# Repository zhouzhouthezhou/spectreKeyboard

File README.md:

# spectreKeyboard

Based off [design](https://wiki.ai03.com/) by ai03  
Inspiration from [Mysterium TKL](https://github.com/coseyfannitutti/mysterium)

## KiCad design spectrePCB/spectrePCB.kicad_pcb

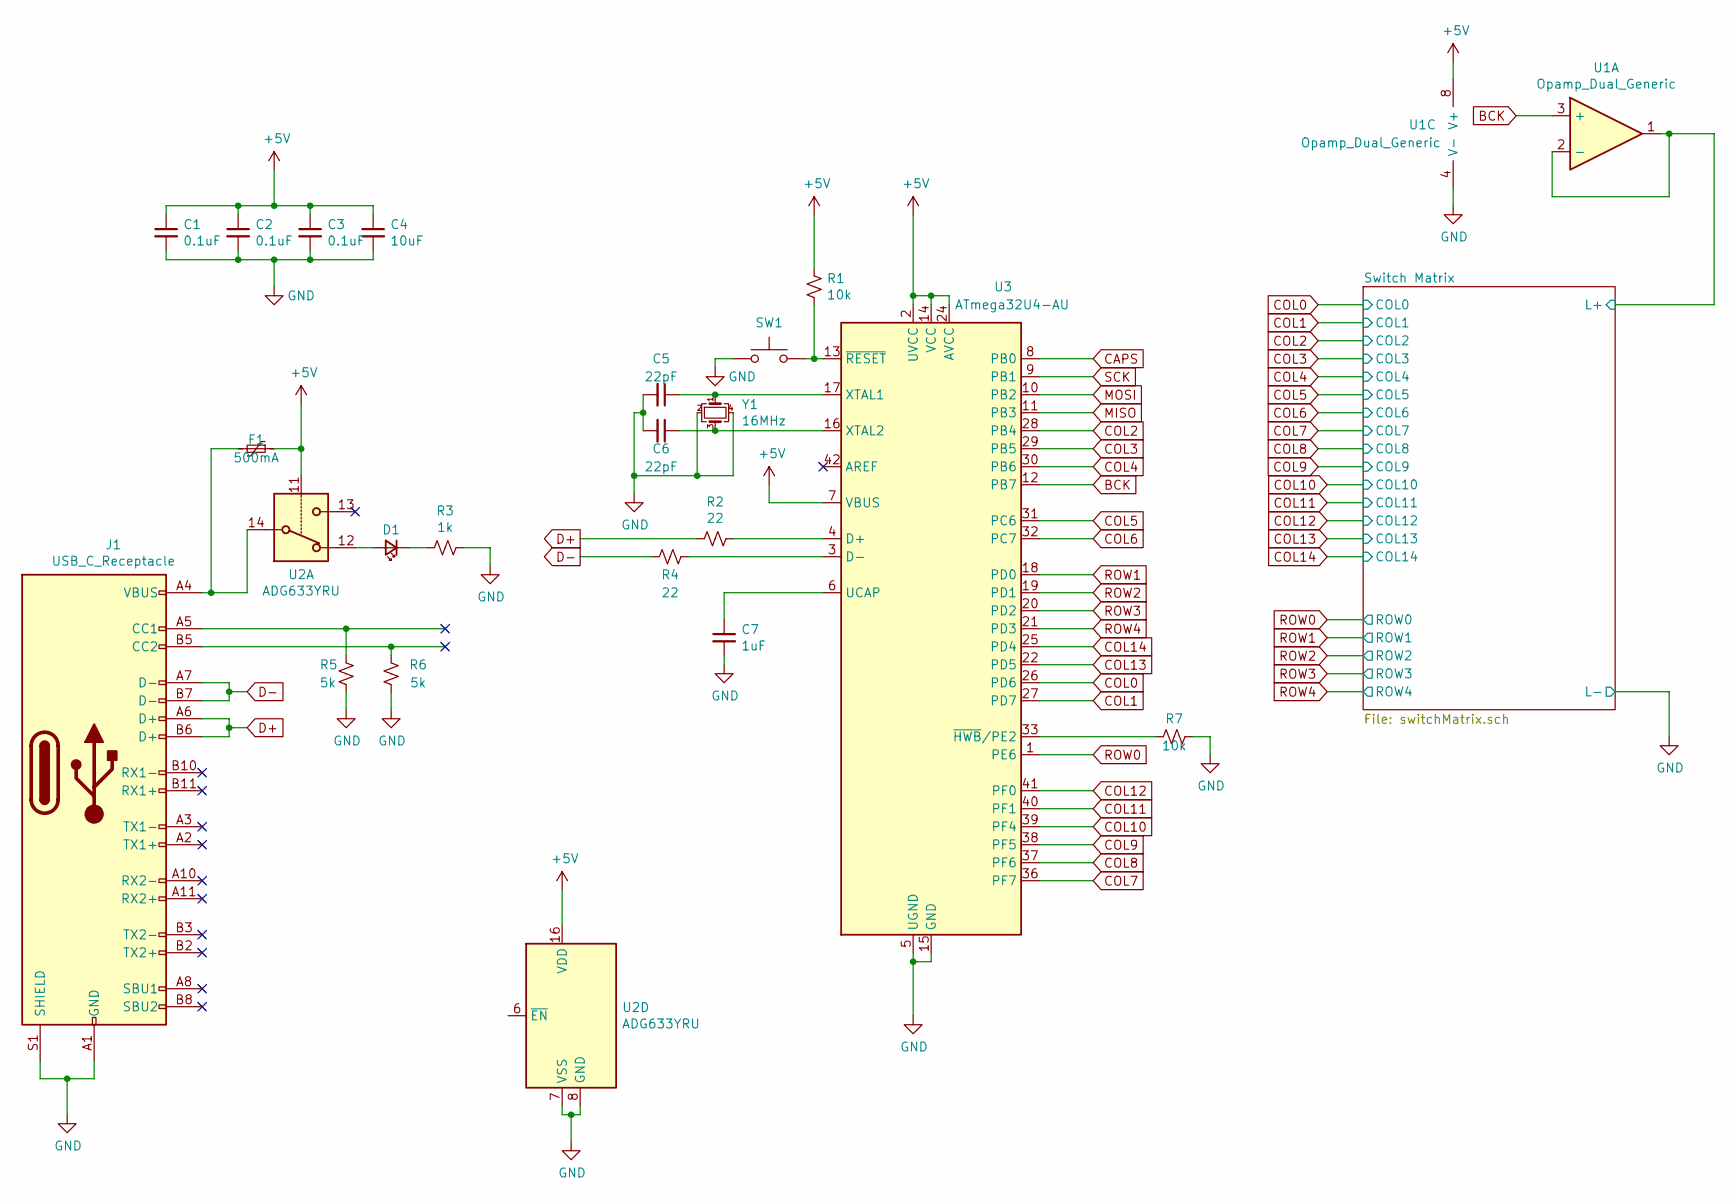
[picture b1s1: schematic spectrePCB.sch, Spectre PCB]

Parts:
C1, C2, C3: 0.1uF; C_0603_1608Metric
C4: 10uF; C_0603_1608Metric
C5, C6: 22pF; C_0603_1608Metric
C7: 1uF; C_0603_1608Metric
D1: LED_Red; LED_0603_1608Metric
F1: 500mA; Fuse_0603_1608Metric
J1: USB_C_Receptacle; USB_C_Receptacle_Amphenol_12401548E4-2A
R1, R7: 10k; R_0603_1608Metric
R2, R4: 22; R_0603_1608Metric
R3: 1k; R_0603_1608Metric
R5, R6: 5k; R_0603_1608Metric
SW1: SW_Push; SW_SPST_TL3305A
U1: Opamp_Dual_Generic; SOIC-8_3.9x4.9mm_P1.27mm
U2: ADG633YRU; TSSOP-20_4.4x6.5mm_P0.65mm
U3: ATmega32U4-AU; TQFP-44_10x10mm_P0.8mm
Y1: 16MHz; Crystal_SMD_3225-4Pin_3.2x2.5mm

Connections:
+5V: C1.1, C2.1, C3.1, C4.1, F1.1, R1.1, U1.8 (V+), U2.11, U2.16 (VDD), U3.2 (UVCC), U3.7 (VBUS), U3.14 (VCC), U3.24 (AVCC), U3.34 (VCC), U3.44 (AVCC); also elsewhere on the board
/Switch Matrix/L+: U1.1, U1.2 (-); also elsewhere on the board
BCK: U1.3 (+), U3.12 (PB7)
COL0: U3.26 (PD6); also elsewhere on the board
COL1: U3.27 (PD7); also elsewhere on the board
COL2: U3.28 (PB4); also elsewhere on the board
COL3: U3.29 (PB5); also elsewhere on the board
COL4: U3.30 (PB6); also elsewhere on the board
COL5: U3.31 (PC6); also elsewhere on the board
COL6: U3.32 (PC7); also elsewhere on the board
COL7: U3.36 (PF7); also elsewhere on the board
COL8: U3.37 (PF6); also elsewhere on the board
COL9: U3.38 (PF5); also elsewhere on the board
COL10: U3.39 (PF4); also elsewhere on the board
COL11: U3.40 (PF1); also elsewhere on the board
COL12: U3.41 (PF0); also elsewhere on the board
COL13: U3.22 (PD5); also elsewhere on the board
COL14: U3.25 (PD4); also elsewhere on the board
D+: J1.A6 (D+), J1.B6 (D+), R2.2
D-: J1.A7 (D-), J1.B7 (D-), R4.2
GND: C1.2, C2.2, C3.2, C4.2, C5.2, C6.2, C7.2, J1.A1 (GND), J1.A12 (GND), J1.B1 (GND), J1.B12 (GND), J1.S1 (SHIELD), R3.1, R5.1, R6.1, R7.1, SW1.1, U1.4 (V-), U2.7 (VSS), U2.8 (GND), U3.5 (UGND), U3.15 (GND), U3.23 (GND), U3.35 (GND), U3.43 (GND), Y1.2, Y1.4; also elsewhere on the board
unnamed: C5.1, U3.17 (XTAL1), Y1.1
unnamed: C6.1, U3.16 (XTAL2), Y1.3
unnamed: C7.1, U3.6 (UCAP)
unnamed: D1.1 (K), R3.2
unnamed: D1.2 (A), U2.12
unnamed: F1.2, J1.A4 (VBUS), J1.A9 (VBUS), J1.B4 (VBUS), J1.B9 (VBUS), U2.14
unnamed: J1.A5 (CC1), R5.2
unnamed: J1.B5 (CC2), R6.2
unnamed: R1.2, SW1.2, U3.13 (~RESET)
unnamed: R2.1, U3.4 (D+)
unnamed: R4.1, U3.3 (D-)
unnamed: R7.2, U3.33 (~HWB~/PE2)
ROW0: U3.1 (PE6); also elsewhere on the board
ROW1: U3.18 (PD0); also elsewhere on the board
ROW2: U3.19 (PD1); also elsewhere on the board
ROW3: U3.20 (PD2); also elsewhere on the board
ROW4: U3.21 (PD3); also elsewhere on the board

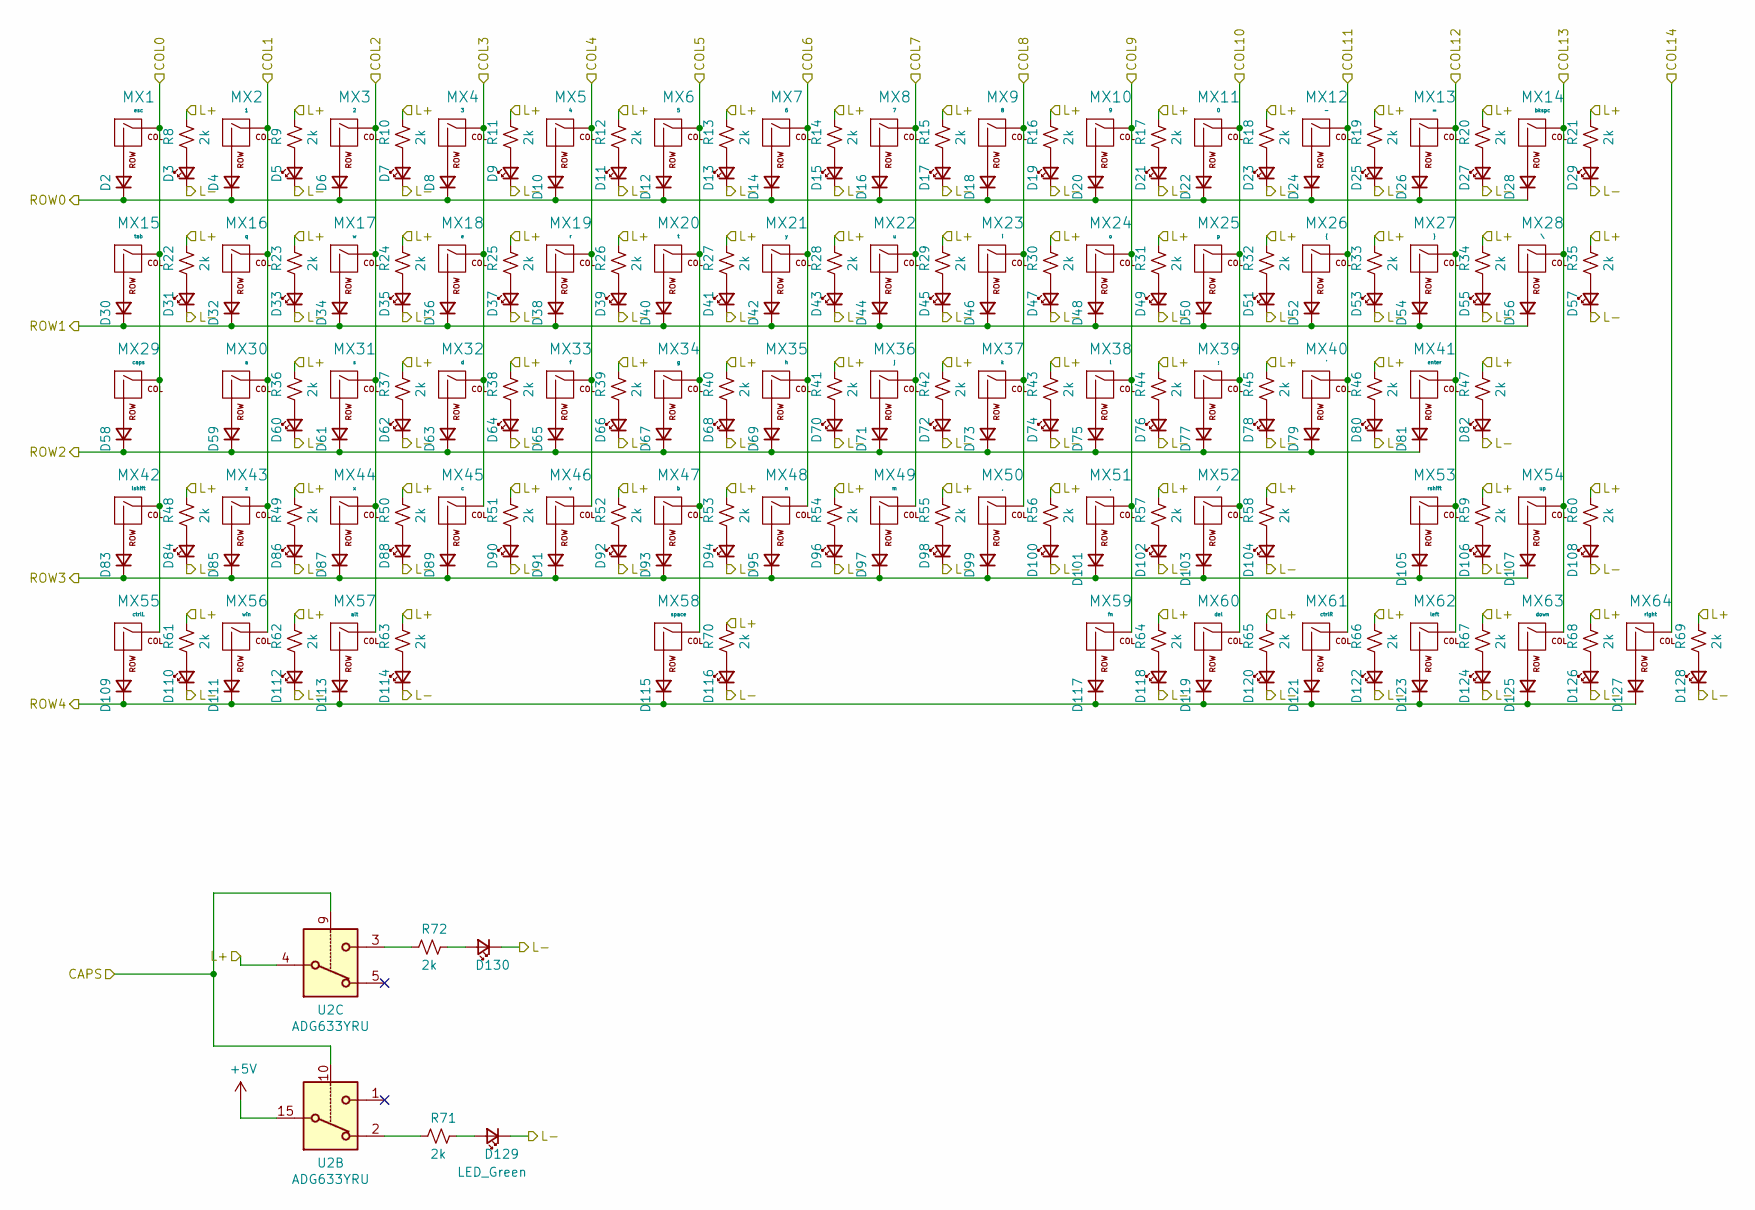
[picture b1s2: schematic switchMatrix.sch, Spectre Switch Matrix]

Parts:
D2, D4, D6, D8, D10, D12, D14, D16, D18, D20, D22, D24, D26, D28, D30, D32, D34, D36, D38, D40, D42, D44, D46, D48, D50, D52, D54, D56, D58, D59, D61, D63, D65, D67, D69, D71, D73, D75, D77, D79, D81, D83, D85, D87, D89, D91, D93, D95, D97, D99, D101, D103, D105, D107, D109, D111, D113, D115, D117, D119, D121, D123, D125, D127: D_Small; D_0603_1608Metric
D3, D5, D7, D9, D11, D13, D15, D17, D19, D21, D23, D25, D27, D29, D31, D33, D35, D37, D39, D41, D43, D45, D47, D49, D51, D53, D55, D57, D60, D62, D64, D66, D68, D70, D72, D74, D76, D78, D80, D82, D84, D86, D88, D90, D92, D94, D96, D98, D100, D102, D104, D106, D108, D110, D112, D114, D116, D118, D120, D122, D124, D126, D128, D130: LED_White; LED_0603_1608Metric
D129: LED_Green; LED_0603_1608Metric
MX1: esc; MX-1U-NoLED
MX2: 1; MX-1U-NoLED
MX3: 2; MX-1U-NoLED
MX4: 3; MX-1U-NoLED
MX5: 4; MX-1U-NoLED
MX6: 5; MX-1U-NoLED
MX7: 6; MX-1U-NoLED
MX8: 7; MX-1U-NoLED
MX9: 8; MX-1U-NoLED
MX10: 9; MX-1U-NoLED
MX11: 0; MX-1U-NoLED
MX12: -; MX-1U-NoLED
MX13: =; MX-1U-NoLED
MX14: bkspc; MX-2U-NoLED
MX15: tab; MX-1.5U-NoLED
MX16: q; MX-1U-NoLED
MX17: w; MX-1U-NoLED
MX18: e; MX-1U-NoLED
MX19: r; MX-1U-NoLED
MX20: t; MX-1U-NoLED
MX21: y; MX-1U-NoLED
MX22: u; MX-1U-NoLED
MX23: i; MX-1U-NoLED
MX24: o; MX-1U-NoLED
MX25: p; MX-1U-NoLED
MX26: {; MX-1U-NoLED
MX27: }; MX-1U-NoLED
MX28: \\; MX-1.5U-NoLED
MX29: caps; MX-1.75U-NoLED
MX30: a; MX-1U-NoLED
MX31: s; MX-1U-NoLED
MX32: d; MX-1U-NoLED
MX33: f; MX-1U-NoLED
MX34: g; MX-1U-NoLED
MX35: h; MX-1U-NoLED
MX36: j; MX-1U-NoLED
MX37: k; MX-1U-NoLED
MX38: l; MX-1U-NoLED
MX39: ;; MX-1U-NoLED
MX40: '; MX-1U-NoLED
MX41: enter; MX-2.25U-NoLED
MX42: lshift; MX-2.25U-NoLED
MX43: z; MX-1U-NoLED
MX44: x; MX-1U-NoLED
MX45: c; MX-1U-NoLED
MX46: v; MX-1U-NoLED
MX47: b; MX-1U-NoLED
MX48: n; MX-1U-NoLED
MX49: m; MX-1U-NoLED
MX50: ,; MX-1U-NoLED
MX51: .; MX-1U-NoLED
MX52: /; MX-1U-NoLED
MX53: rshift; MX-2.75U-NoLED
MX54: up; MX-1U-NoLED
MX55: ctrlL; MX-1.25U-NoLED
MX56: win; MX-1.25U-NoLED
MX57: alt; MX-1.25U-NoLED
MX58: space; MX-6.25U-NoLED
MX59: fn; MX-1.25U-NoLED
MX60: del; MX-1.25U-NoLED
MX61: ctrlR; MX-1.25U-NoLED
MX62: left; MX-1U-NoLED
MX63: down; MX-1U-NoLED
MX64: right; MX-1U-NoLED
R8, R9, R10, R11, R12, R13, R14, R15, R16, R17, R18, R19, R20, R21, R22, R23, R24, R25, R26, R27, R28, R29, R30, R31, R32, R33, R34, R35, R36, R37, R38, R39, R40, R41, R42, R43, R44, R45, R46, R47, R48, R49, R50, R51, R52, R53, R54, R55, R56, R57, R58, R59, R60, R61, R62, R63, R64, R65, R66, R67, R68, R69, R70, R71, R72: 2k; R_0603_1608Metric
U2: ADG633YRU; TSSOP-20_4.4x6.5mm_P0.65mm

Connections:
+5V: U2.15; also elsewhere on the board
/Switch Matrix/CAPS: U2.9, U2.10
/Switch Matrix/L+: R8.1, R9.1, R10.1, R11.1, R12.1, R13.1, R14.1, R15.1, R16.1, R17.1, R18.1, R19.1, R20.1, R21.1, R22.1, R23.1, R24.1, R25.1, R26.1, R27.1, R28.1, R29.1, R30.1, R31.1, R32.1, R33.1, R34.1, R35.1, R36.1, R37.1, R38.1, R39.1, R40.1, R41.1, R42.1, R43.1, R44.1, R45.1, R46.1, R47.1, R48.1, R49.1, R50.1, R51.1, R52.1, R53.1, R54.1, R55.1, R56.1, R57.1, R58.1, R59.1, R60.1, R61.1, R62.1, R63.1, R64.1, R65.1, R66.1, R67.1, R68.1, R69.1, R70.1, U2.4; also elsewhere on the board
COL0: MX1.1 (COL), MX15.1 (COL), MX29.1 (COL), MX42.1 (COL), MX55.1 (COL); also elsewhere on the board
COL1: MX2.1 (COL), MX16.1 (COL), MX30.1 (COL), MX43.1 (COL), MX56.1 (COL); also elsewhere on the board
COL2: MX3.1 (COL), MX17.1 (COL), MX31.1 (COL), MX44.1 (COL), MX57.1 (COL); also elsewhere on the board
COL3: MX4.1 (COL), MX18.1 (COL), MX32.1 (COL), MX45.1 (COL); also elsewhere on the board
COL4: MX5.1 (COL), MX19.1 (COL), MX33.1 (COL), MX46.1 (COL); also elsewhere on the board
COL5: MX6.1 (COL), MX20.1 (COL), MX34.1 (COL), MX47.1 (COL), MX58.1 (COL); also elsewhere on the board
COL6: MX7.1 (COL), MX21.1 (COL), MX35.1 (COL), MX48.1 (COL); also elsewhere on the board
COL7: MX8.1 (COL), MX22.1 (COL), MX36.1 (COL), MX49.1 (COL); also elsewhere on the board
COL8: MX9.1 (COL), MX23.1 (COL), MX37.1 (COL), MX50.1 (COL); also elsewhere on the board
COL9: MX10.1 (COL), MX24.1 (COL), MX38.1 (COL), MX51.1 (COL), MX59.1 (COL); also elsewhere on the board
COL10: MX11.1 (COL), MX25.1 (COL), MX39.1 (COL), MX52.1 (COL), MX60.1 (COL); also elsewhere on the board
COL11: MX12.1 (COL), MX26.1 (COL), MX40.1 (COL), MX61.1 (COL); also elsewhere on the board
COL12: MX13.1 (COL), MX27.1 (COL), MX41.1 (COL), MX53.1 (COL), MX62.1 (COL); also elsewhere on the board
COL13: MX14.1 (COL), MX28.1 (COL), MX54.1 (COL), MX63.1 (COL); also elsewhere on the board
COL14: MX64.1 (COL); also elsewhere on the board
GND: D3.1 (K), D5.1 (K), D7.1 (K), D9.1 (K), D11.1 (K), D13.1 (K), D15.1 (K), D17.1 (K), D19.1 (K), D21.1 (K), D23.1 (K), D25.1 (K), D27.1 (K), D29.1 (K), D31.1 (K), D33.1 (K), D35.1 (K), D37.1 (K), D39.1 (K), D41.1 (K), D43.1 (K), D45.1 (K), D47.1 (K), D49.1 (K), D51.1 (K), D53.1 (K), D55.1 (K), D57.1 (K), D60.1 (K), D62.1 (K), D64.1 (K), D66.1 (K), D68.1 (K), D70.1 (K), D72.1 (K), D74.1 (K), D76.1 (K), D78.1 (K), D80.1 (K), D82.1 (K), D84.1 (K), D86.1 (K), D88.1 (K), D90.1 (K), D92.1 (K), D94.1 (K), D96.1 (K), D98.1 (K), D100.1 (K), D102.1 (K), D104.1 (K), D106.1 (K), D108.1 (K), D110.1 (K), D112.1 (K), D114.1 (K), D116.1 (K), D118.1 (K), D120.1 (K), D122.1 (K), D124.1 (K), D126.1 (K), D128.1 (K), D129.1 (K), D130.1 (K); also elsewhere on the board
unnamed: D2.2 (A), MX1.2 (ROW)
unnamed: D3.2 (A), R8.2
unnamed: D4.2 (A), MX2.2 (ROW)
unnamed: D5.2 (A), R9.2
unnamed: D6.2 (A), MX3.2 (ROW)
unnamed: D7.2 (A), R10.2
unnamed: D8.2 (A), MX4.2 (ROW)
unnamed: D9.2 (A), R11.2
unnamed: D10.2 (A), MX5.2 (ROW)
unnamed: D11.2 (A), R12.2
unnamed: D12.2 (A), MX6.2 (ROW)
unnamed: D13.2 (A), R13.2
unnamed: D14.2 (A), MX7.2 (ROW)
unnamed: D15.2 (A), R14.2
unnamed: D16.2 (A), MX8.2 (ROW)
unnamed: D17.2 (A), R15.2
unnamed: D18.2 (A), MX9.2 (ROW)
unnamed: D19.2 (A), R16.2
unnamed: D20.2 (A), MX10.2 (ROW)
unnamed: D21.2 (A), R17.2
unnamed: D22.2 (A), MX11.2 (ROW)
unnamed: D23.2 (A), R18.2
unnamed: D24.2 (A), MX12.2 (ROW)
unnamed: D25.2 (A), R19.2
unnamed: D26.2 (A), MX13.2 (ROW)
unnamed: D27.2 (A), R20.2
unnamed: D28.2 (A), MX14.2 (ROW)
unnamed: D29.2 (A), R21.2
unnamed: D30.2 (A), MX15.2 (ROW)
unnamed: D31.2 (A), R22.2
unnamed: D32.2 (A), MX16.2 (ROW)
unnamed: D33.2 (A), R23.2
unnamed: D34.2 (A), MX17.2 (ROW)
unnamed: D35.2 (A), R24.2
unnamed: D36.2 (A), MX18.2 (ROW)
unnamed: D37.2 (A), R25.2
unnamed: D38.2 (A), MX19.2 (ROW)
unnamed: D39.2 (A), R26.2
unnamed: D40.2 (A), MX20.2 (ROW)
unnamed: D41.2 (A), R27.2
unnamed: D42.2 (A), MX21.2 (ROW)
unnamed: D43.2 (A), R28.2
unnamed: D44.2 (A), MX22.2 (ROW)
unnamed: D45.2 (A), R29.2
unnamed: D46.2 (A), MX23.2 (ROW)
unnamed: D47.2 (A), R30.2
unnamed: D48.2 (A), MX24.2 (ROW)
unnamed: D49.2 (A), R31.2
unnamed: D50.2 (A), MX25.2 (ROW)
unnamed: D51.2 (A), R32.2
unnamed: D52.2 (A), MX26.2 (ROW)
unnamed: D53.2 (A), R33.2
unnamed: D54.2 (A), MX27.2 (ROW)
unnamed: D55.2 (A), R34.2
unnamed: D56.2 (A), MX28.2 (ROW)
unnamed: D57.2 (A), R35.2
unnamed: D58.2 (A), MX29.2 (ROW)
unnamed: D59.2 (A), MX30.2 (ROW)
unnamed: D60.2 (A), R36.2
unnamed: D61.2 (A), MX31.2 (ROW)
unnamed: D62.2 (A), R37.2
unnamed: D63.2 (A), MX32.2 (ROW)
unnamed: D64.2 (A), R38.2
unnamed: D65.2 (A), MX33.2 (ROW)
unnamed: D66.2 (A), R39.2
unnamed: D67.2 (A), MX34.2 (ROW)
unnamed: D68.2 (A), R40.2
unnamed: D69.2 (A), MX35.2 (ROW)
unnamed: D70.2 (A), R41.2
unnamed: D71.2 (A), MX36.2 (ROW)
unnamed: D72.2 (A), R42.2
unnamed: D73.2 (A), MX37.2 (ROW)
unnamed: D74.2 (A), R43.2
unnamed: D75.2 (A), MX38.2 (ROW)
unnamed: D76.2 (A), R44.2
unnamed: D77.2 (A), MX39.2 (ROW)
unnamed: D78.2 (A), R45.2
unnamed: D79.2 (A), MX40.2 (ROW)
unnamed: D80.2 (A), R46.2
unnamed: D81.2 (A), MX41.2 (ROW)
unnamed: D82.2 (A), R47.2
unnamed: D83.2 (A), MX42.2 (ROW)
unnamed: D84.2 (A), R48.2
unnamed: D85.2 (A), MX43.2 (ROW)
unnamed: D86.2 (A), R49.2
unnamed: D87.2 (A), MX44.2 (ROW)
unnamed: D88.2 (A), R50.2
unnamed: D89.2 (A), MX45.2 (ROW)
unnamed: D90.2 (A), R51.2
unnamed: D91.2 (A), MX46.2 (ROW)
unnamed: D92.2 (A), R52.2
unnamed: D93.2 (A), MX47.2 (ROW)
unnamed: D94.2 (A), R53.2
unnamed: D95.2 (A), MX48.2 (ROW)
unnamed: D96.2 (A), R54.2
unnamed: D97.2 (A), MX49.2 (ROW)
unnamed: D98.2 (A), R55.2
unnamed: D99.2 (A), MX50.2 (ROW)
unnamed: D100.2 (A), R56.2
unnamed: D101.2 (A), MX51.2 (ROW)
unnamed: D102.2 (A), R57.2
unnamed: D103.2 (A), MX52.2 (ROW)
unnamed: D104.2 (A), R58.2
unnamed: D105.2 (A), MX53.2 (ROW)
unnamed: D106.2 (A), R59.2
unnamed: D107.2 (A), MX54.2 (ROW)
unnamed: D108.2 (A), R60.2
unnamed: D109.2 (A), MX55.2 (ROW)
unnamed: D110.2 (A), R61.2
unnamed: D111.2 (A), MX56.2 (ROW)
unnamed: D112.2 (A), R62.2
unnamed: D113.2 (A), MX57.2 (ROW)
unnamed: D114.2 (A), R63.2
unnamed: D115.2 (A), MX58.2 (ROW)
unnamed: D116.2 (A), R70.2
unnamed: D117.2 (A), MX59.2 (ROW)
unnamed: D118.2 (A), R64.2
unnamed: D119.2 (A), MX60.2 (ROW)
unnamed: D120.2 (A), R65.2
unnamed: D121.2 (A), MX61.2 (ROW)
unnamed: D122.2 (A), R66.2
unnamed: D123.2 (A), MX62.2 (ROW)
unnamed: D124.2 (A), R67.2
unnamed: D125.2 (A), MX63.2 (ROW)
unnamed: D126.2 (A), R68.2
unnamed: D127.2 (A), MX64.2 (ROW)
unnamed: D128.2 (A), R69.2
unnamed: D129.2 (A), R71.1
unnamed: D130.2 (A), R72.1
unnamed: R71.2, U2.2
unnamed: R72.2, U2.3
ROW0: D2.1 (K), D4.1 (K), D6.1 (K), D8.1 (K), D10.1 (K), D12.1 (K), D14.1 (K), D16.1 (K), D18.1 (K), D20.1 (K), D22.1 (K), D24.1 (K), D26.1 (K), D28.1 (K); also elsewhere on the board
ROW1: D30.1 (K), D32.1 (K), D34.1 (K), D36.1 (K), D38.1 (K), D40.1 (K), D42.1 (K), D44.1 (K), D46.1 (K), D48.1 (K), D50.1 (K), D52.1 (K), D54.1 (K), D56.1 (K); also elsewhere on the board
ROW2: D58.1 (K), D59.1 (K), D61.1 (K), D63.1 (K), D65.1 (K), D67.1 (K), D69.1 (K), D71.1 (K), D73.1 (K), D75.1 (K), D77.1 (K), D79.1 (K), D81.1 (K); also elsewhere on the board
ROW3: D83.1 (K), D85.1 (K), D87.1 (K), D89.1 (K), D91.1 (K), D93.1 (K), D95.1 (K), D97.1 (K), D99.1 (K), D101.1 (K), D103.1 (K), D105.1 (K), D107.1 (K); also elsewhere on the board
ROW4: D109.1 (K), D111.1 (K), D113.1 (K), D115.1 (K), D117.1 (K), D119.1 (K), D121.1 (K), D123.1 (K), D125.1 (K), D127.1 (K); also elsewhere on the board

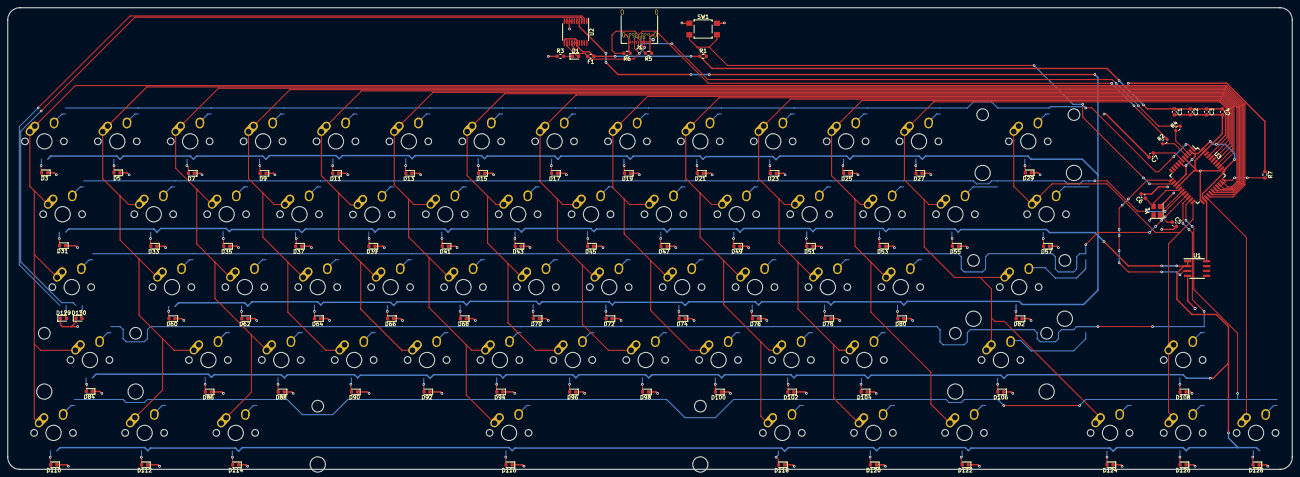
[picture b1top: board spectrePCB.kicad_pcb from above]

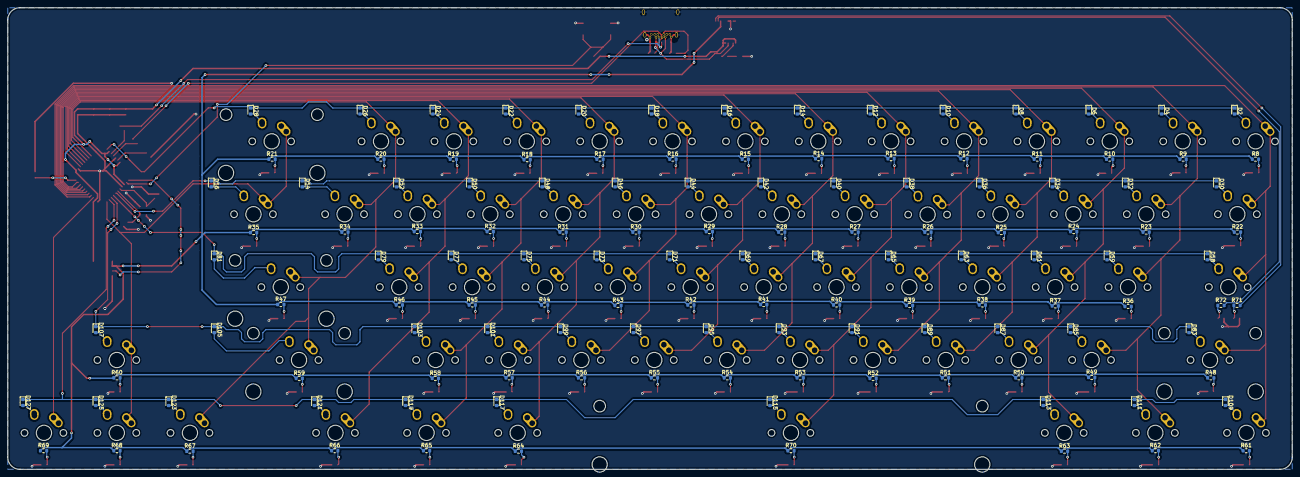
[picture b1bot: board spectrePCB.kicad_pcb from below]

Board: 2 copper layers, 335.8 x 120.7 mm, 280 parts (129 on the bottom side), 170 nets.

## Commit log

2021-03-17 Adding submodules for schematic parts
2021-03-17 move submodules
2021-03-18 Added microcontroler and USB-C schematics
2021-03-20 added switch and led matricies and pinouts to atmega
2021-03-23 added initial qmk firmware build, untested
2021-03-23 finished capslock key and pin mapping. Rev1 done
2021-03-23 fixed big decoup cap not being big
2021-03-23 added footprints to components
2021-03-23 dove into the rats nest. I regret everything
2021-04-06 placed resistors, added edges, fixing GND net
2021-04-07 finished routing pcb
